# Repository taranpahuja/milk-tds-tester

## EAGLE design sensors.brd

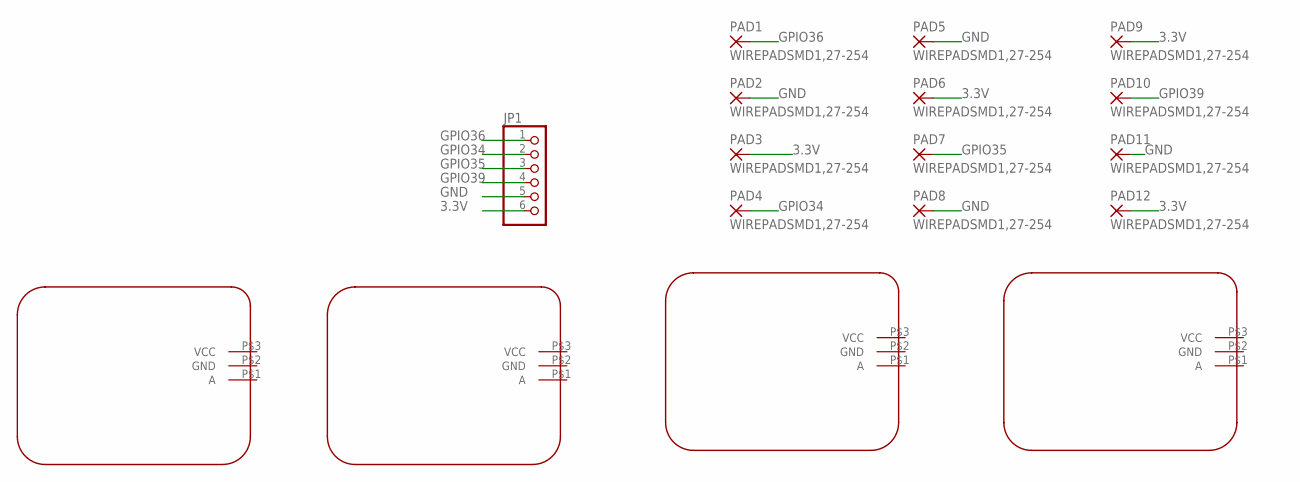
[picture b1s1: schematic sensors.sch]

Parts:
JP1: PINHD-1X6; 1X06
PAD1, PAD2, PAD3, PAD4, PAD5, PAD6, PAD7, PAD8, PAD9, PAD10, PAD11, PAD12: WIREPADSMD1,27-254; SMD1,27-2,54
U$1, U$2, U$3, U$4: SEN0244; PACKAGE

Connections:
3.3V: JP1.6, PAD3.1, PAD6.1, PAD9.1, PAD12.1
GND: JP1.5, PAD2.1, PAD5.1, PAD8.1, PAD11.1
GPIO34: JP1.2, PAD4.1
GPIO35: JP1.3, PAD7.1
GPIO36: JP1.1, PAD1.1
GPIO39: JP1.4, PAD10.1

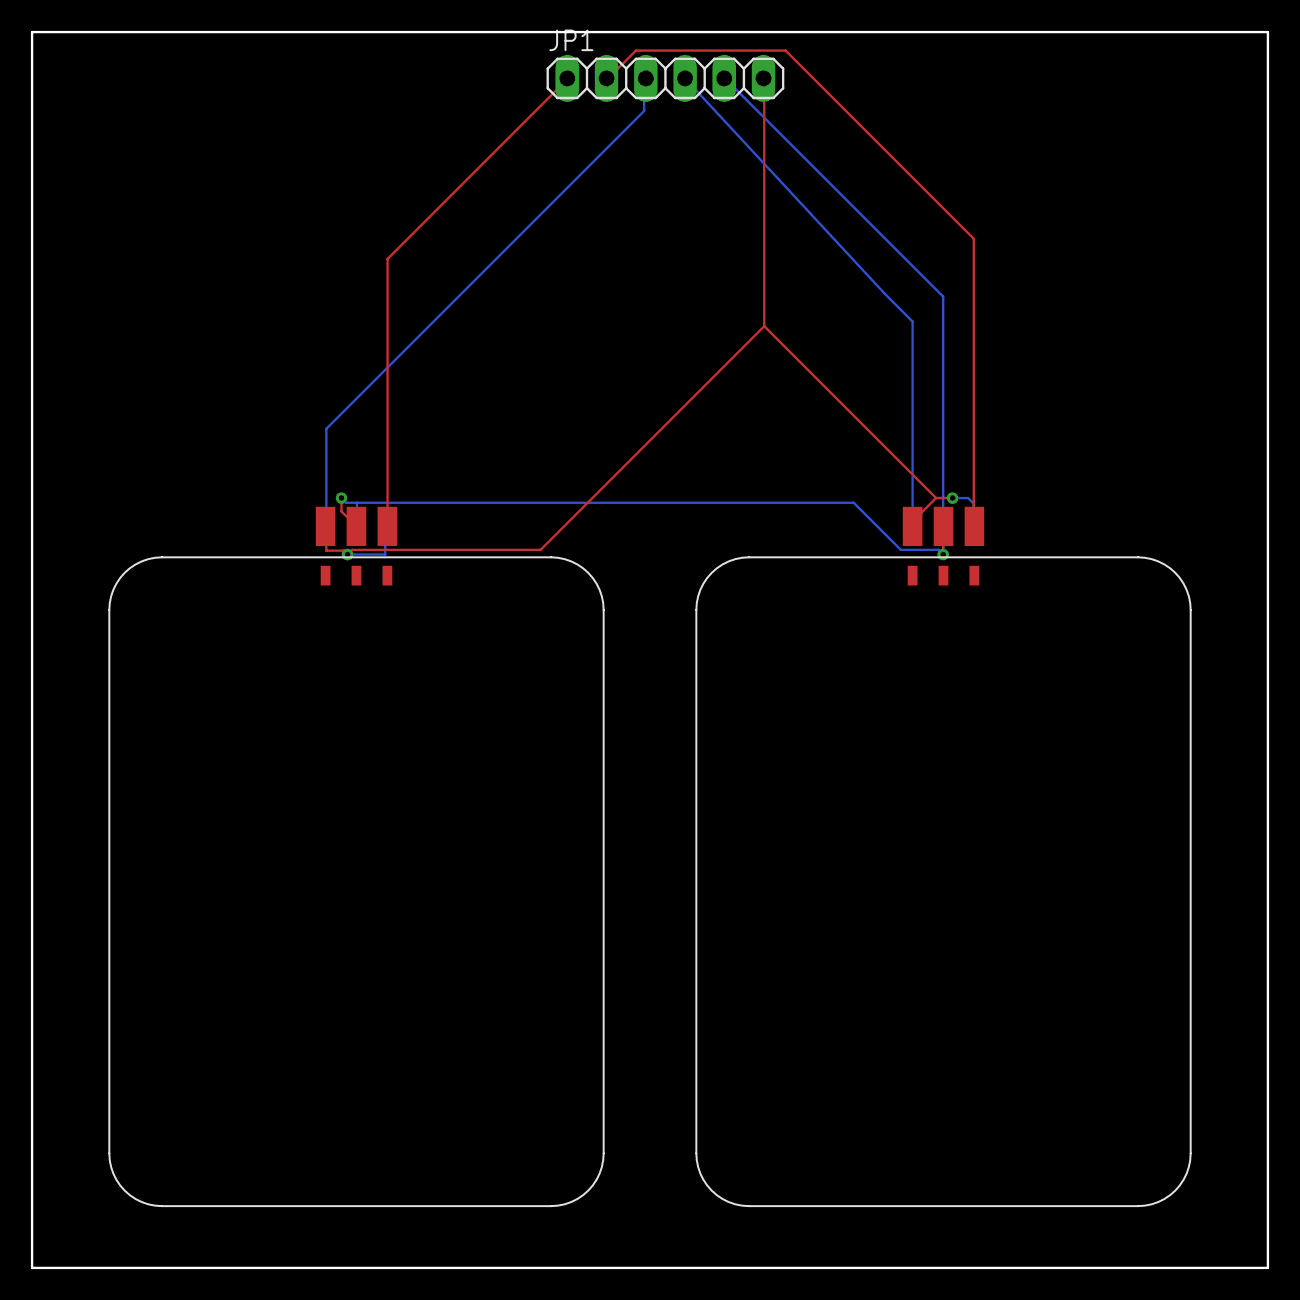
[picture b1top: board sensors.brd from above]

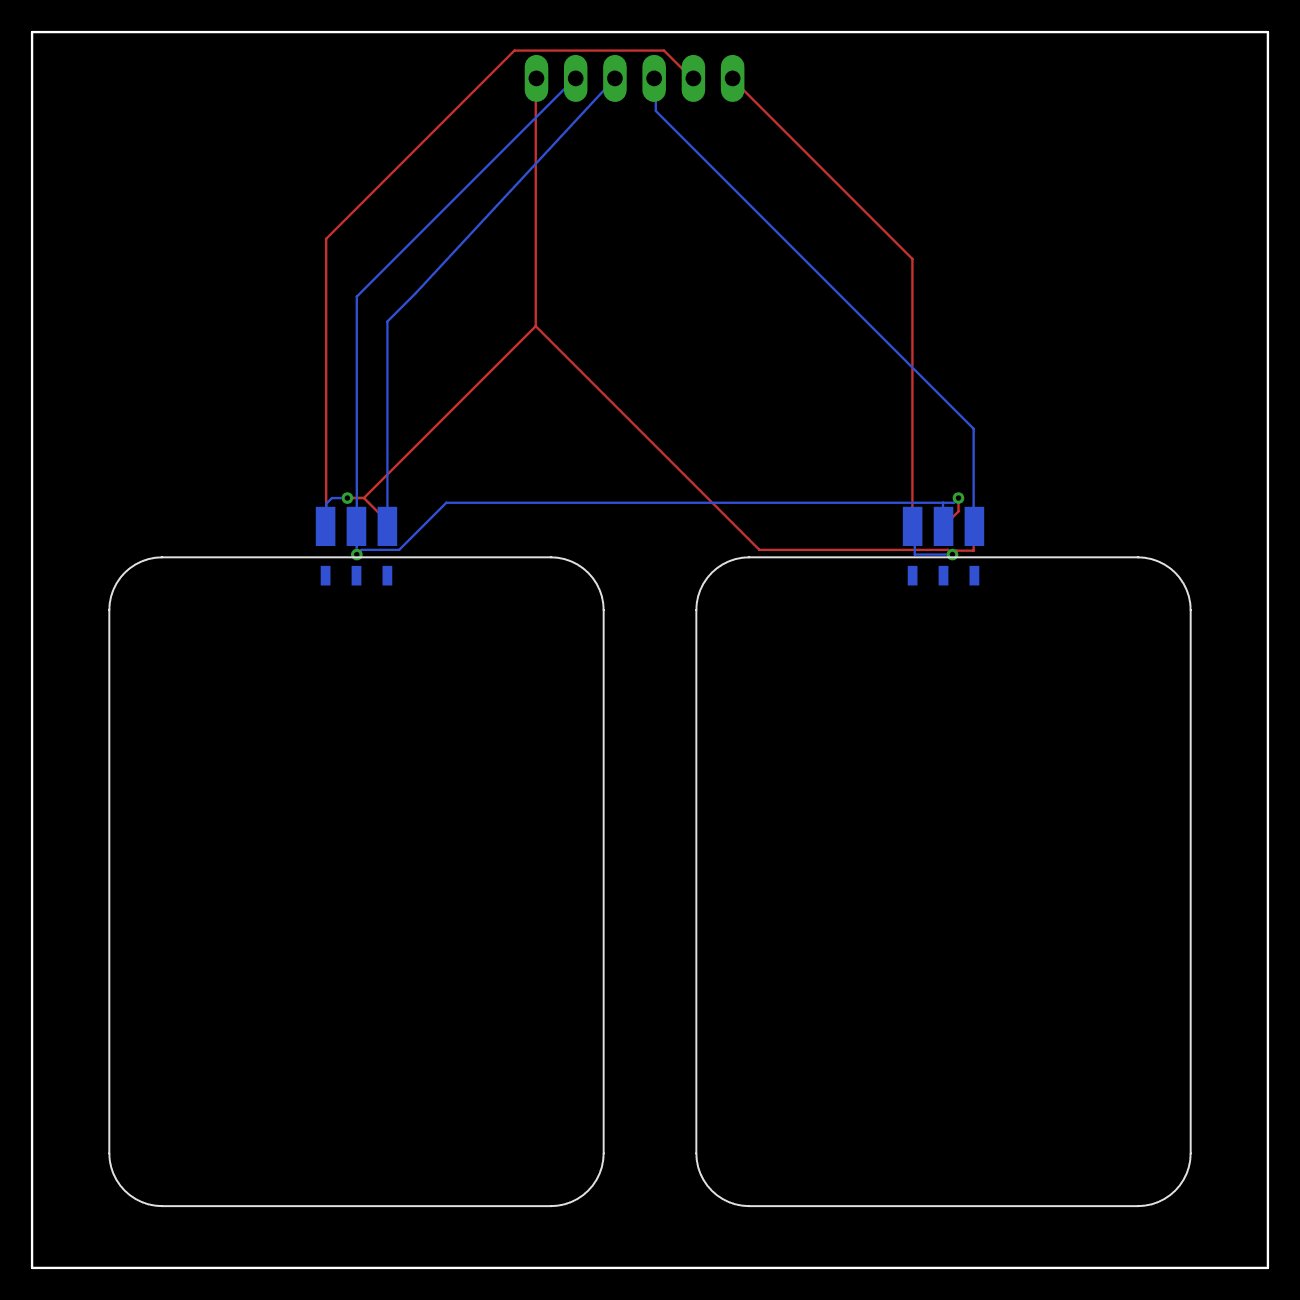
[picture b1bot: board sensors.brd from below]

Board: 2 copper layers, 80.0 x 80.0 mm, 17 parts (8 on the bottom side), 6 nets.

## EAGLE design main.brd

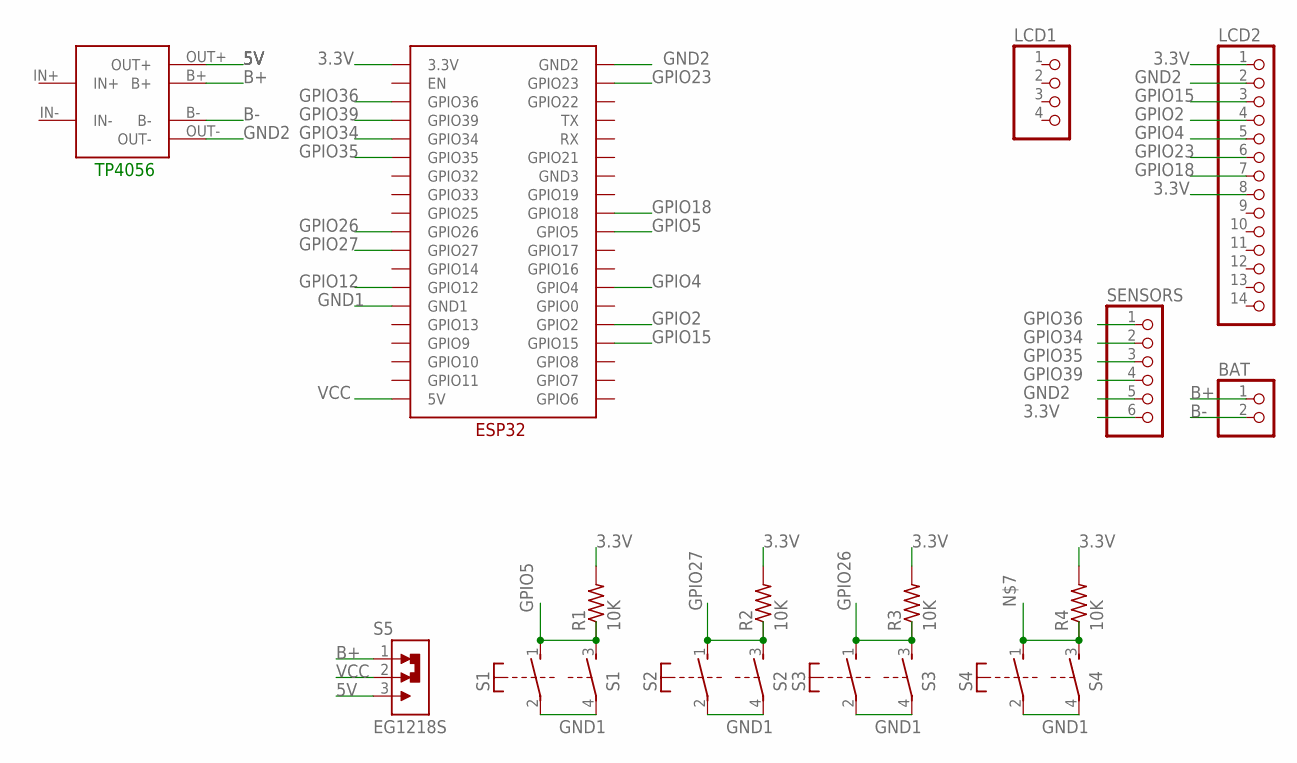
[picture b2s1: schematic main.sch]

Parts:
BAT: PINHD-1X2; 1X02
LCD1: PINHD-1X4; 1X04
LCD2: PINHD-1X14; 1X14
R1, R2, R3, R4: 10K; R0603
S1, S2, S3, S4: PVA1; PVA1F
S5: EG1218S; SW_EG1218
SENSORS: PINHD-1X6; 1X06
U$1: TP4056-PTH
U$2: ESP32

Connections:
3.3V: LCD2.1, LCD2.8, R1.2, R2.2, R3.2, R4.2, SENSORS.6, U$2.3.3V
5V: S5.3 (NO), U$1.OUT+
B+: BAT.1, S5.1 (NC), U$1.B+
B-: BAT.2, U$1.B-
GND1: S1.2, S1.4, U$2.GND1
GND2: LCD2.2, SENSORS.5, U$1.OUT-, U$2.GND2
GPIO2: LCD2.4, U$2.GPIO2
GPIO4: LCD2.5, U$2.GPIO4
GPIO5: R1.1, S1.1 (S), S1.3 (S), U$2.GPIO5
GPIO12: U$2.GPIO12
GPIO15: LCD2.3, U$2.GPIO15
GPIO18: LCD2.7, U$2.GPIO18
GPIO23: LCD2.6, U$2.GPIO23
GPIO26: R3.1, S3.1 (S), S3.3 (S), U$2.GPIO26
GPIO27: R2.1, S2.1 (S), S2.3 (S), U$2.GPIO27
GPIO34: SENSORS.2, U$2.GPIO34
GPIO35: SENSORS.3, U$2.GPIO35
GPIO36: SENSORS.1, U$2.GPIO36
GPIO39: SENSORS.4, U$2.GPIO39
unnamed: S2.2, S2.4
unnamed: S3.2, S3.4
unnamed: S4.2, S4.4
unnamed: R4.1, S4.1 (S), S4.3 (S)
VCC: S5.2 (COM), U$2.5V

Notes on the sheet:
TP4056

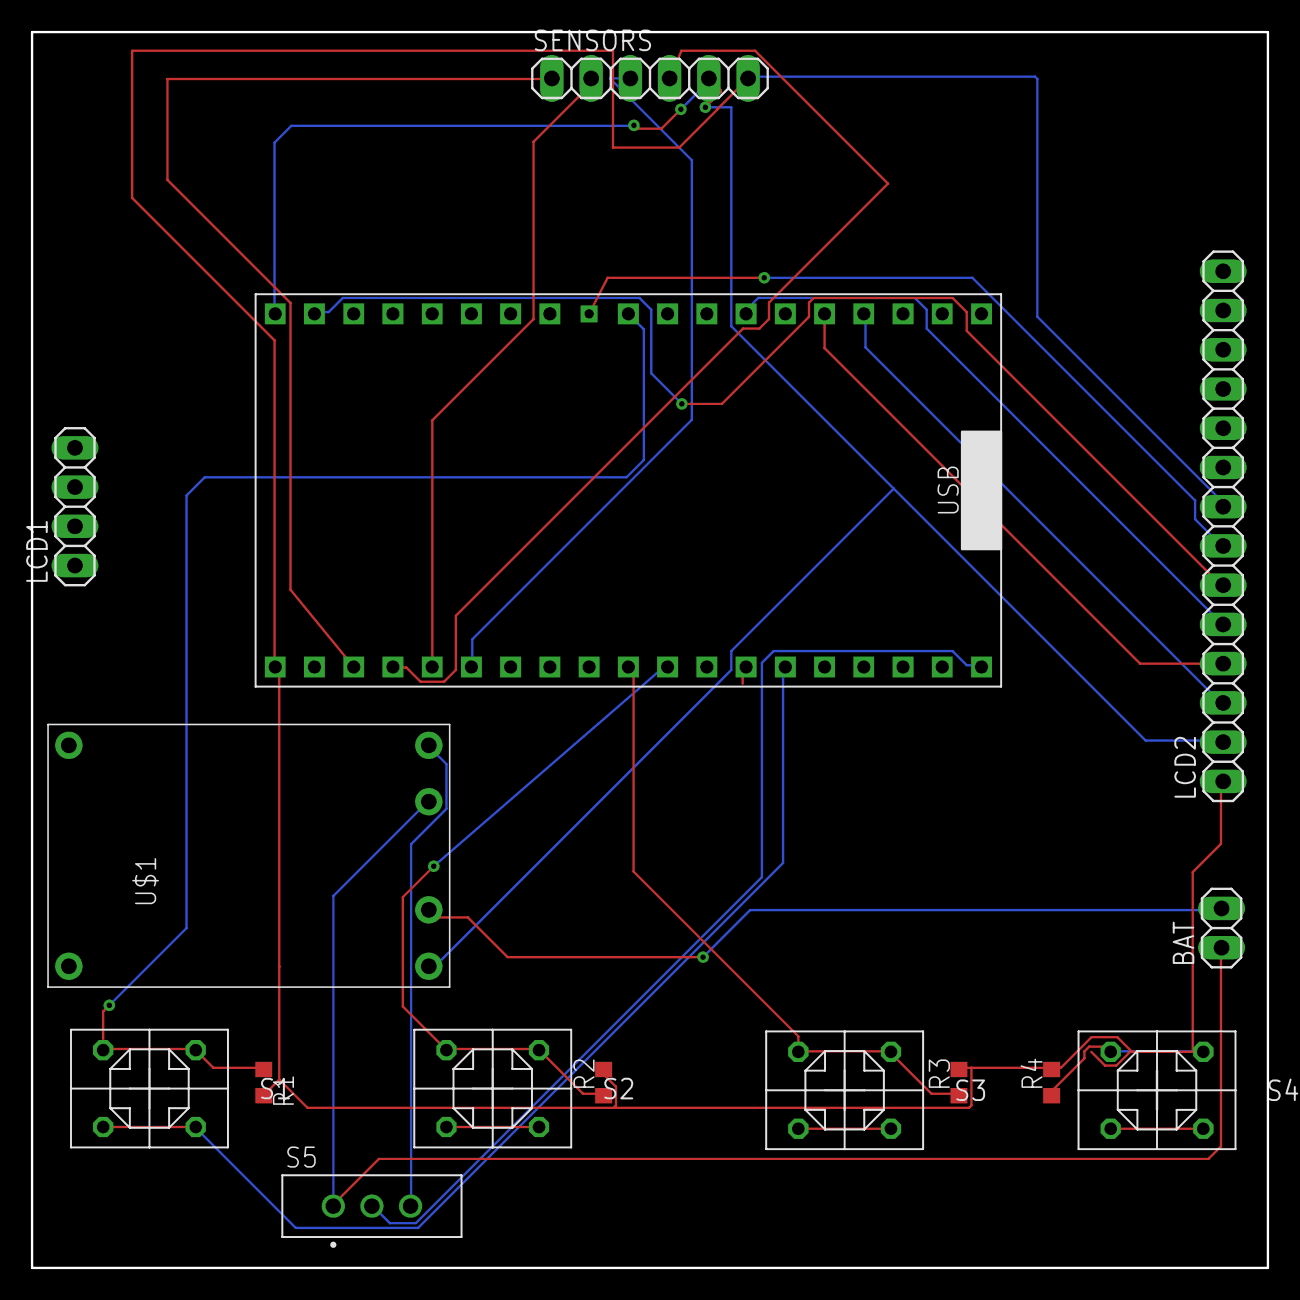
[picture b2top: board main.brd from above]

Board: 2 copper layers, 80.0 x 80.0 mm, 15 parts (0 on the bottom side), 23 nets.

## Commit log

2025-07-16 all code
2025-07-16 schematics and boards
